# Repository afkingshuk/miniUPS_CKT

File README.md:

# miniUPS_CKT

Mini UPS for household router and ONU.
for 4 devices (12v, 12v, 9v, 5v).

Charging circuit and battery is not included.

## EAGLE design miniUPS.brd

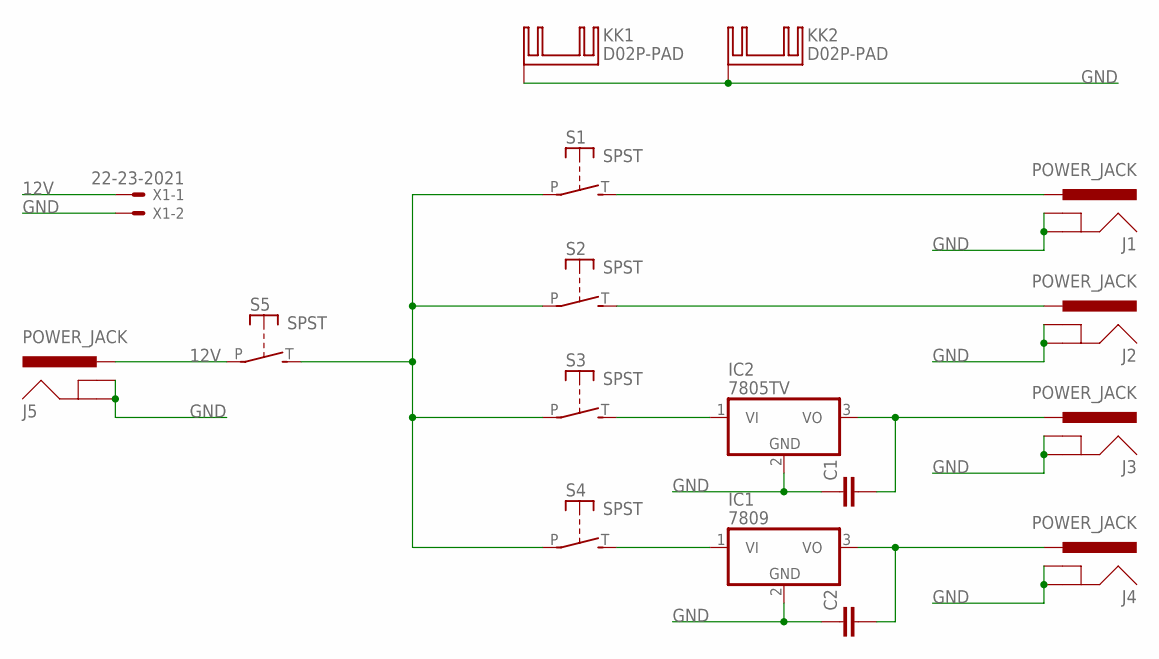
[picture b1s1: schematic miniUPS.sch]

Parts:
C1, C2: CAPPTH2; CAP-PTH-SMALL2
IC1: 7809; TO220V
IC2: 7805TV; TO220V
J1, J2, J3, J4, J5: POWER_JACK; POWER_JACK_PTH
KK1, KK2: D02P-PAD; D02PA-PAD
S1, S2, S3, S4, S5: SPST; JUDCOSPST
X1: 22-23-2021

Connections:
12V: J5.PWR, S5.P, X1.1
GND: C1.1, C2.1, IC1.2 (GND), IC2.2 (GND), J1.GND, J1.GNDBREAK, J2.GND, J2.GNDBREAK, J3.GND, J3.GNDBREAK, J4.GND, J4.GNDBREAK, J5.GND, J5.GNDBREAK, KK1.B, KK2.B, X1.2
unnamed: J1.PWR, S1.T (S)
unnamed: J2.PWR, S2.T (S)
unnamed: C1.2, IC2.3 (VO), J3.PWR
unnamed: C2.2, IC1.3 (VO), J4.PWR
unnamed: IC2.1 (VI), S3.T (S)
unnamed: IC1.1 (VI), S4.T (S)
unnamed: S1.P, S2.P, S3.P, S4.P, S5.T (S)

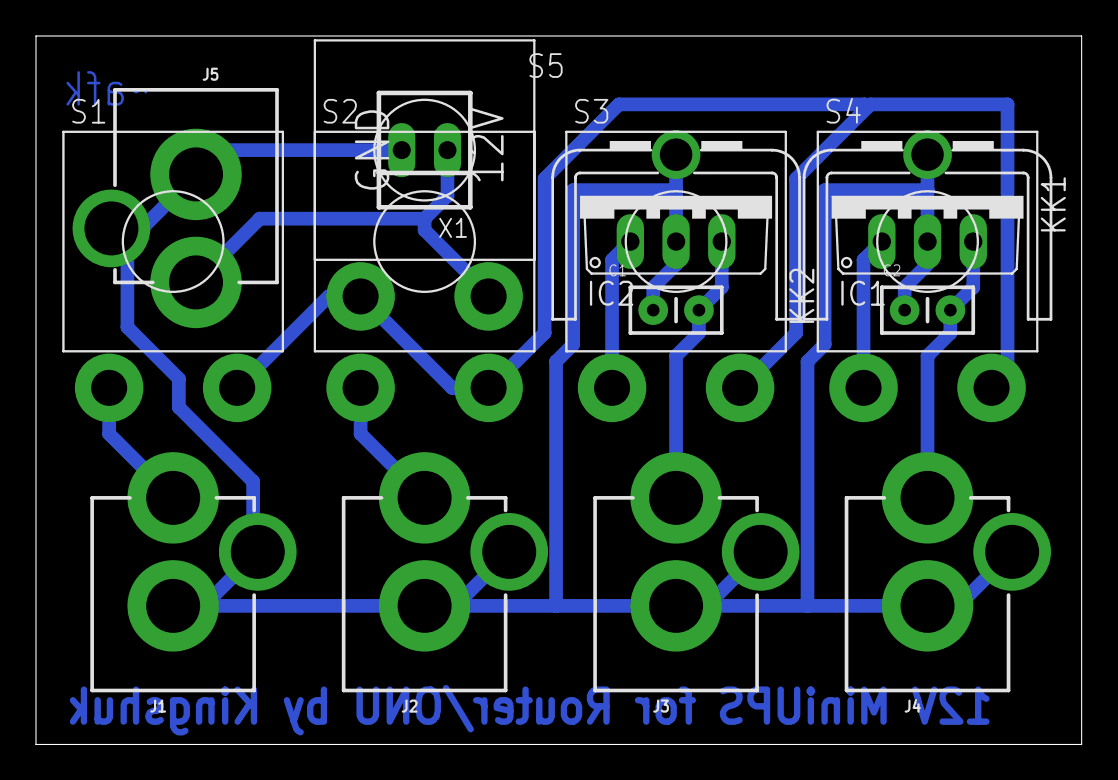
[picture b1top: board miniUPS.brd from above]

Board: 2 copper layers, 58.1 x 39.4 mm, 17 parts (0 on the bottom side), 9 nets.

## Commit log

2021-03-31 init
    Mini UPS for household router and ONU.
    for 4 devices (12v, 12v, 9v, 5v).
    Charging circuit and battery is not included.
2021-03-31 init

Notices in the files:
parts and their libraries:
SparkFun-Connectors: Licensing: Creative Commons ShareAlike 4.0 International - https://creativecommons.org/licenses/by-sa/4.0
